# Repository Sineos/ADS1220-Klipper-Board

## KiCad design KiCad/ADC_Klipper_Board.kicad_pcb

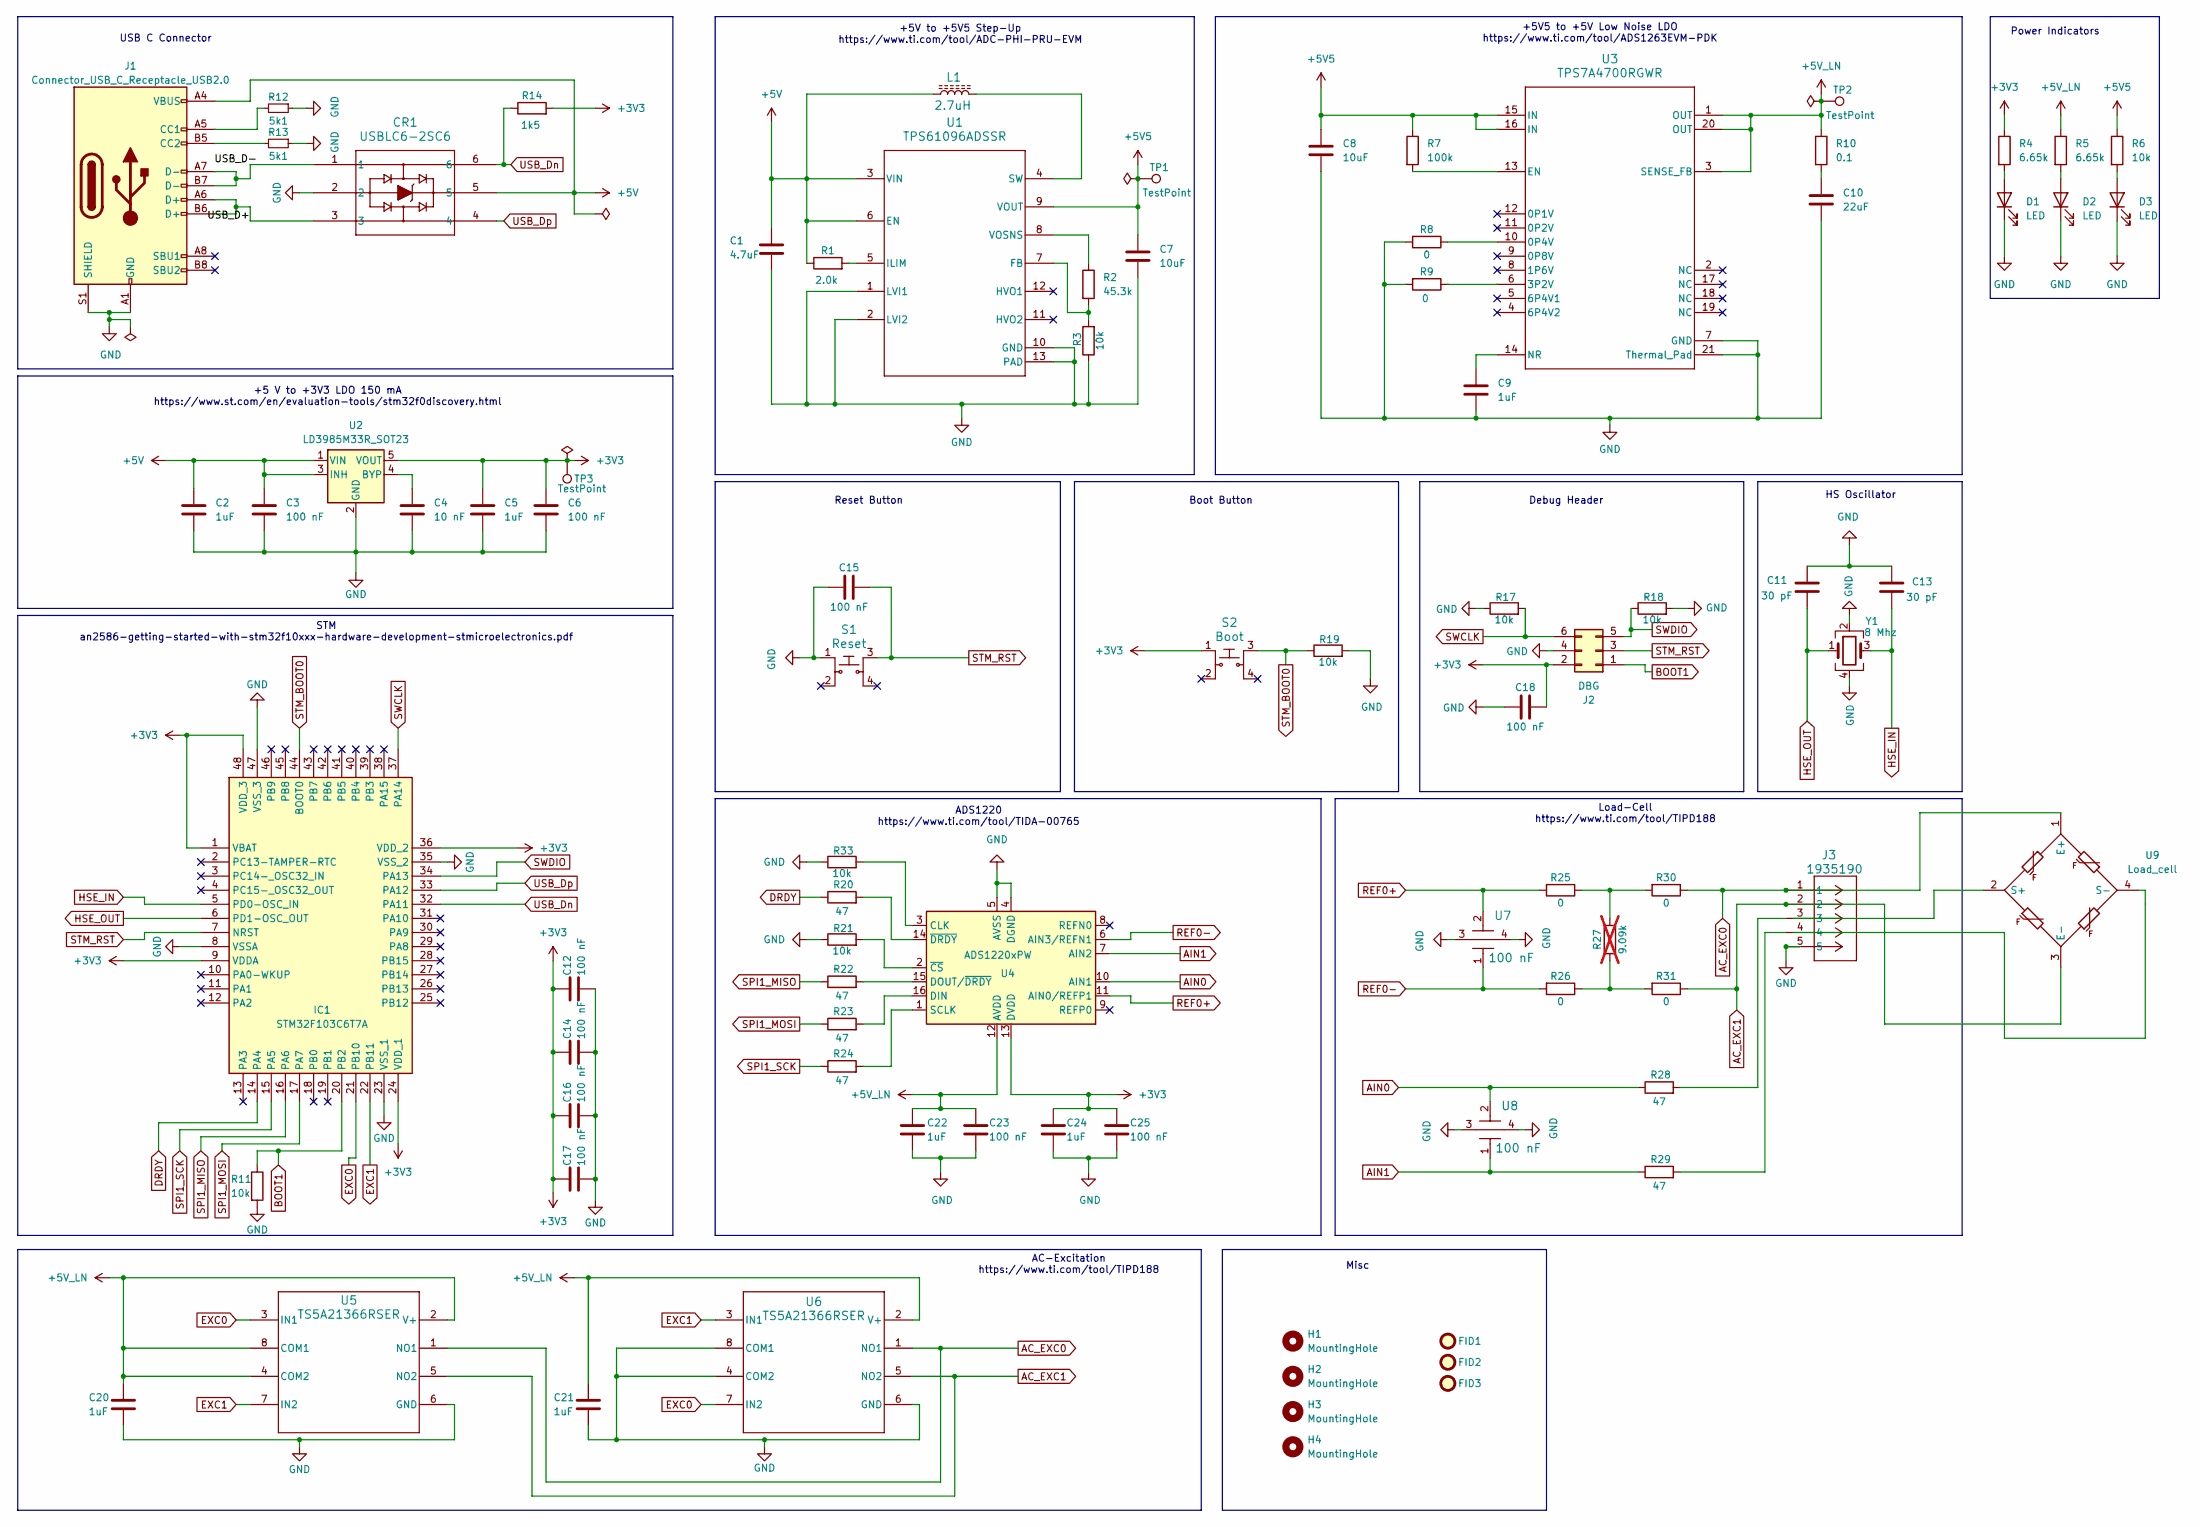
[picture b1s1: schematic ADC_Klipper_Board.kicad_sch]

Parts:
C1: 4.7uF; C_0805_2012Metric; Manufacturer_Part_Number GRM21BR71A475KE51L; LCSC C415536
C2, C5, C9, C20, C21, C22, C24: 1uF; C_0603_1608Metric; Manufacturer_Part_Number GCJ188R71E105KA01D; LCSC C908553
C3, C6, C12, C14, C15, C16, C17, C18, C23, C25: 100 nF; C_0603_1608Metric; Manufacturer_Part_Number CC0603KRX7R7BB104; LCSC C108079
C4: 10 nF; C_0603_1608Metric; Manufacturer_Part_Number CC0603KRX7R9BB103; LCSC C100042
C7, C8: 10uF; C_1206_3216Metric; Manufacturer_Part_Number C1206C106K3RACTU; LCSC C2168111
C10: 22uF; C_1210_3225Metric; Manufacturer_Part_Number GRM32ER71E226KE15L; LCSC C21397
C11, C13: 30 pF; C_0603_1608Metric; Manufacturer_Part_Number AC0603JRNPO9BN300; LCSC C2191217
CR1: USBLC6-2SC6; SOT23-6L_STM; Manufacturer_Part_Number USBLC6-2SC6; LCSC C2827654
D1, D2, D3: LED; LED_0805_2012Metric; Manufacturer_Part_Number APT2012LZGCK; LCSC C5569446
FID1, FID2, FID3: Fiducial; Fiducial_1mm_Mask2mm
H1, H2, H3, H4: MountingHole; MountingHole_3.2mm_M3_ISO7380
IC1: STM32F103C6T7A; QFP50P900X900X160-48N; Manufacturer_Part_Number STM32F103C6T7A; LCSC C222074
J1: Connector_USB_C_Receptacle_USB2.0; TYPE-C-31-M-12; Manufacturer_Part_Number TYPE-C-31-M-12; LCSC C5337088
J2: DBG; PinHeader_2x03_P2.54mm_Vertical; Manufacturer_Part_Number 2.54-2*3P; LCSC C65114
J3: 1935190; CONN_1935190_PXC; Manufacturer_Part_Number 1935190; LCSC C6047339
L1: 2.7uH; IND_5028_TDK; Manufacturer_Part_Number VLCF5020T-2R7N1R7; LCSC C307836
R1: 2.0k; R_0603_1608Metric; Manufacturer_Part_Number R0603RXX202XF10LTS; LCSC C267576
R2: 45.3k; R_0603_1608Metric; Manufacturer_Part_Number ERJ3EKF4532V; LCSC C403233
R3, R6, R11, R17, R18, R19, R21, R33: 10k; R_0603_1608Metric; Manufacturer_Part_Number RT0603FRE0710KL; LCSC C469659
R4, R5: 6.65k; R_0603_1608Metric; Manufacturer_Part_Number AC0603FR-076K65L; LCSC C228025
R7: 100k; R_0603_1608Metric; Manufacturer_Part_Number RT0603FRE07100KL; LCSC C728638
R8, R9, R25, R26, R30, R31: 0; R_0603_1608Metric; Manufacturer_Part_Number RC0603JR-070RL; LCSC C95177
R10: 0.1; R_0603_1608Metric; Manufacturer_Part_Number UCR03EVPFLR100; LCSC C880952
R12, R13: 5k1; R_0603_1608Metric; Manufacturer_Part_Number CRCW06035K10FKEA; LCSC C844933
R14: 1k5; R_0603_1608Metric; Manufacturer_Part_Number RMC1/16K152FTP; LCSC C340503
R20, R22, R23, R24, R28, R29: 47; R_0603_1608Metric; Manufacturer_Part_Number CRCW060347R0FKEA; LCSC C511383
R27: 9.09k; R_0603_1608Metric; Manufacturer_Part_Number ERJ-3EKF9091V; not fitted
S1: Reset; SWITCH_43SMTR92LFS; Manufacturer_Part_Number PTS645SM43SMTR92; LCSC C221880
S2: Boot; SWITCH_43SMTR92LFS; Manufacturer_Part_Number PTS645SM43SMTR92; LCSC C221880
TP1, TP2, TP3: TestPoint; TestPoint_Pad_D2.0mm
U1: TPS61096ADSSR; DSS0012A; Manufacturer_Part_Number TPS61096ADSSR; LCSC C2862062
U2: LD3985M33R_SOT23; SOT-23-5; Manufacturer_Part_Number LD3985M33R; LCSC C46243
U3: TPS7A4700RGWR; RGW0020A-IPC_A; Manufacturer_Part_Number TPS7A4700RGWR; LCSC C114839
U4: ADS1220xPW; SOP65P640X120-16N; Manufacturer_Part_Number ADS1220xPW; LCSC C48263
U5, U6: TS5A21366RSER; RSE0008A; Manufacturer_Part_Number TS5A21366RSER
U7, U8: 100 nF; X15; Manufacturer_Part_Number 250X15W104MV4E; LCSC C111274
U9: Load_cell
Y1: 8 Mhz; Crystal_SMD_5032-4Pin_5.0x3.2mm; Manufacturer_Part_Number XL1SI-111-8M; LCSC C20617600

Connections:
+3V3: C5.1, C6.1, C12.1, C14.1, C16.1, C17.1, C18.2, C24.1, C25.1, IC1.1 (VBAT), IC1.9 (VDDA), IC1.24 (VDD_1), IC1.36 (VDD_2), IC1.48 (VDD_3), J2.2, R4.1, R14.2, S2.1, TP3.1, U2.5 (VOUT), U4.13 (DVDD)
+5V: C1.1, C2.1, C3.1, CR1.5, J1.A4 (VBUS), J1.A9 (VBUS), J1.B4 (VBUS), J1.B9 (VBUS), L1.1, R1.1, U1.3 (VIN), U1.6 (EN), U2.1 (VIN), U2.3 (INH)
+5V5: C7.1, C8.1, R6.1, R7.1, TP1.1, U1.9 (VOUT), U3.15 (IN), U3.16 (IN)
+5V_LN: C20.1, C21.1, C22.1, C23.1, R5.1, R10.1, TP2.1, U3.1 (OUT), U3.3 (SENSE_FB), U3.20 (OUT), U4.12 (AVDD), U5.2 (V+), U5.4 (COM2), U5.8 (COM1), U6.2 (V+)
/USB_D+: CR1.3, J1.A6 (D+), J1.B6 (D+)
/USB_D-: CR1.1, J1.A7 (D-), J1.B7 (D-)
AC_EXC0: J3.1, R30.1, U5.1 (NO1), U6.1 (NO1), U9.1 (E+)
AC_EXC1: J3.2, R31.1, U5.5 (NO2), U6.5 (NO2), U9.3 (E-)
AIN0: R28.1, U4.10 (AIN1), U8.2
AIN1: R29.1, U4.7 (AIN2), U8.1
BOOT1: IC1.20 (PB2), J2.1, R11.1
DRDY: IC1.14 (PA4), R20.1
EXC0: IC1.21 (PB10), U5.3 (IN1), U6.7 (IN2)
EXC1: IC1.22 (PB11), U5.7 (IN2), U6.3 (IN1)
GND: C1.2, C2.2, C3.2, C4.2, C5.2, C6.2, C7.2, C8.2, C9.2, C10.2, C11.1, C12.2, C13.1, C14.2, C15.1, C16.2, C17.2, C18.1, C20.2, C21.2, C22.2, C23.2, C24.2, C25.2, CR1.2, D1.1 (K), D2.1 (K), D3.1 (K), IC1.8 (VSSA), IC1.23 (VSS_1), IC1.35 (VSS_2), IC1.47 (VSS_3), J1.A1 (GND), J1.A12 (GND), J1.B1 (GND), J1.B12 (GND), J1.S1 (SHIELD), J2.4, J3.5, R3.1, R8.2, R9.2, R11.2, R12.1, R13.1, R17.1, R18.2, R19.2, R21.1, R33.1, S1.1, U1.1 (LVI1), U1.2 (LVI2), U1.10 (GND), U1.13 (PAD), U1.V, U2.2 (GND), U3.7 (GND), U3.21 (Thermal_Pad), U4.4 (DGND), U4.5 (AVSS), U5.6 (GND), U6.4 (COM2), U6.6 (GND), U6.8 (COM1), U7.3, U7.4, U8.3, U8.4, Y1.2, Y1.4
HSE_IN: C13.2, IC1.5 (PD0-OSC_IN), Y1.3
HSE_OUT: C11.2, IC1.6 (PD1-OSC_OUT), Y1.1
unnamed: C10.1, R10.2
unnamed: D1.2 (A), R4.2
unnamed: D2.2 (A), R5.2
unnamed: D3.2 (A), R6.2
unnamed: J1.A5 (CC1), R12.2
unnamed: J1.B5 (CC2), R13.2
unnamed: J3.3, R28.2
unnamed: J3.4, R29.2
unnamed: R25.1, R27.1, R30.2
unnamed: R26.1, R27.2, R31.2
unnamed: R2.2, R3.2, U1.7 (FB)
unnamed: R1.2, U1.5 (ILIM)
unnamed: L1.2, U1.4 (SW)
unnamed: R2.1, U1.8 (VOSNS)
unnamed: C4.1, U2.4 (BYP)
unnamed: R8.1, U3.10 (0P4V)
unnamed: R9.1, U3.6 (3P2V)
unnamed: R7.2, U3.13 (EN)
unnamed: C9.1, U3.14 (NR)
unnamed: R33.2, U4.3 (CLK)
unnamed: R23.2, U4.16 (DIN)
unnamed: R22.2, U4.15 (DOUT/~DRDY)
unnamed: R24.2, U4.1 (SCLK)
unnamed: R21.2, U4.2 (~CS)
unnamed: R20.2, U4.14 (~DRDY)
REF0+: R25.2, U4.11 (AIN0/REFP1), U7.2
REF0-: R26.2, U4.6 (AIN3/REFN1), U7.1
SPI1_MISO: IC1.16 (PA6), R22.1
SPI1_MOSI: IC1.17 (PA7), R23.1
SPI1_SCK: IC1.15 (PA5), R24.1
STM_BOOT0: IC1.44 (BOOT0), R19.1, S2.3
STM_RST: C15.2, IC1.7 (NRST), J2.3, S1.3
SWCLK: IC1.37 (PA14), J2.6, R17.2
SWDIO: IC1.34 (PA13), J2.5, R18.1
USB_Dn: CR1.6, IC1.32 (PA11), R14.1
USB_Dp: CR1.4, IC1.33 (PA12)

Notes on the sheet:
Reset Button
Load-Cell https://www.ti.com/tool/TIPD188
Boot Button
+5V to +5V5 Step-Up https://www.ti.com/tool/ADC-PHI-PRU-EVM
USB C Connector
Misc
ADS1220 https://www.ti.com/tool/TIDA-00765
+5V5 to +5V Low Noise LDO https://www.ti.com/tool/ADS1263EVM-PDK
Debug Header
STM an2586-getting-started-with-stm32f10xxx-hardware-development-stmicroelectronics.pdf
Power Indicators
HS Oscillator
AC-Excitation https://www.ti.com/tool/TIPD188
+5 V to +3V3 LDO 150 mA https://www.st.com/en/evaluation-tools/stm32f0discovery.html

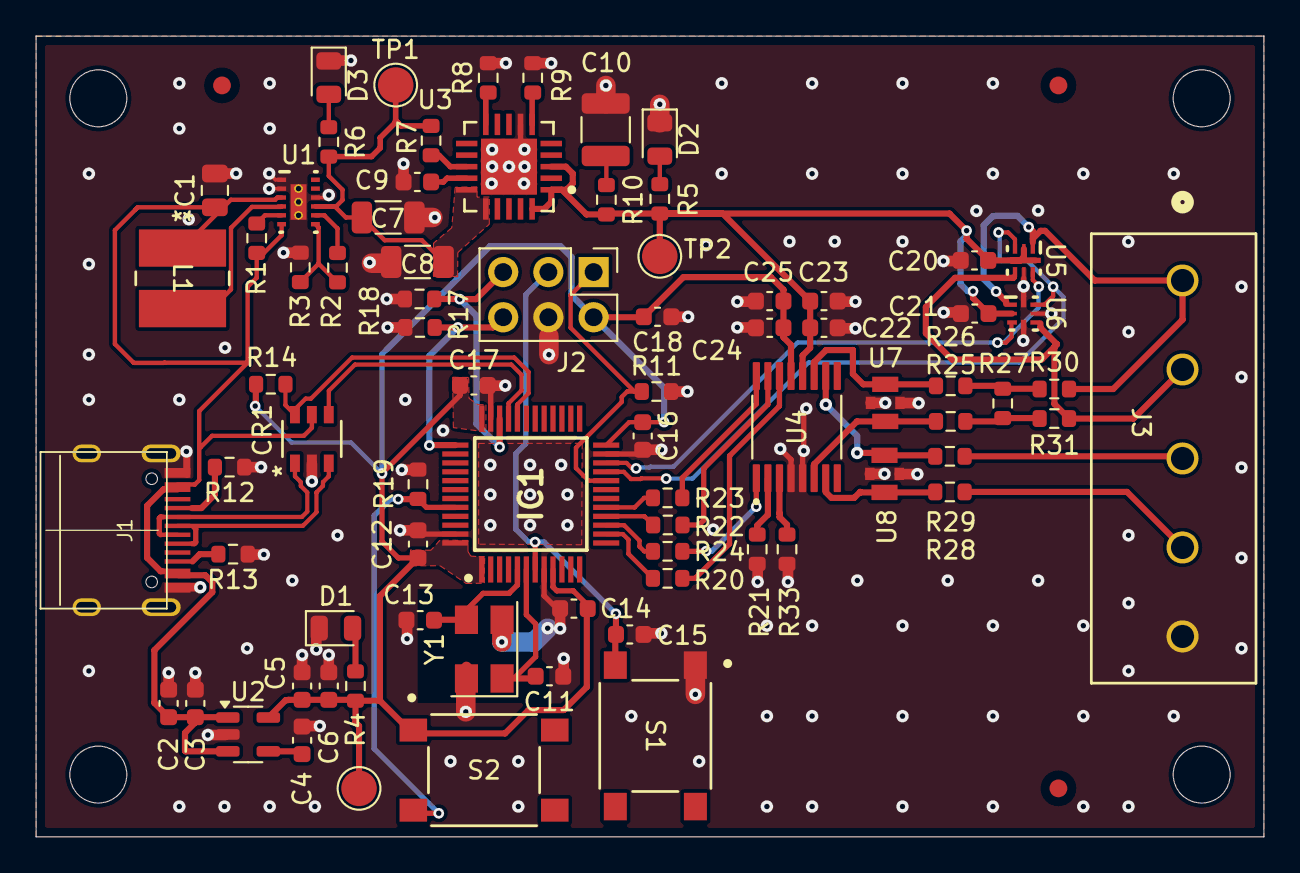
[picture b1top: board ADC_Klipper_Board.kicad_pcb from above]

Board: 4 copper layers, 69.0 x 45.0 mm, 84 parts (0 on the bottom side), 53 nets.

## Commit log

2024-10-07 test
    upd
